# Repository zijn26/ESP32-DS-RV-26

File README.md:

Phần 1 . Hướng dẫn mở dự án kicad 

## 1️⃣ Giới thiệu

Project này được thiết kế bằng **KiCad** và bao gồm:

* **Schematic (sơ đồ nguyên lý)**
* **PCB Layout (mạch in nhiều lớp)**

Tài liệu này hướng dẫn cách mở và xem toàn bộ project bằng **KiCad** trên Windows, Linux hoặc macOS.

---

## 2️⃣ Phần mềm cần cài

Tải và cài đặt :

👉 **KiCad 7 hoặc KiCad 8 hoặc KiCad 9 **

Tải tại:
[https://www.kicad.org](https://www.kicad.org)

> ⚠ Khuyến nghị dùng Kicad 9, phiên bản mà project được tạo ra để tránh lỗi.

---

## 3️⃣ Cấu trúc thư mục project

Sau khi giải nén file ZIP, bạn sẽ thấy thư mục dạng:

```
MyProject/
├── esp32_module.kicad_pro
├── esp32_module.kicad_sch
├── esp32_module.kicad_pcb
├── MyFootprints.pretty
├── ul_myfootprinandsymbol
```

| File         | Chức năng           |
| ------------ | ------------------- |
| `.kicad_pro` | File project chính  |
| `.kicad_sch` | Schematic           |
| `.kicad_pcb` | PCB layout          |
| `.pretty`    | Footprint tùy chỉnh |
| `.kicad_sym` | Symbol tùy chỉnh    |
| `ul_xxxxxxx` | File chứa các footprint và symbol tùy chỉnh   |

---

## 4️⃣ Cách mở project trong KiCad

### Bước 1

Mở **KiCad**

---

### Bước 2

Nhấn **File → Open Project**

---

### Bước 3

Chọn file:

```
MyProject.kicad_pro
```

## 5️⃣ Mở Schematic (Sơ đồ nguyên lý)

Sau khi project mở:

Nhấn **Schematic Editor**

Sau đó sơ đồ nguyên lý sẽ xuất hiện.

---

## 6️⃣ Mở PCB Layout

Trong cửa sổ chính của KiCad:

Nhấn **PCB Editor**

PCB sẽ được mở ra với:

* Các lớp đồng (Top, Bottom, Inner layers)
* Via
* Plane
* Footprint

đang nằm **cùng thư mục với project**

Phần 2 : Thông tin về linh kiên sử dụng , giải thích về sơ đồ nguyên lý và mạch in

Thông tin về linh kiện sử dụng : 
Thầy hãy đọc file LINHKIENSUDUNG.md để biết thông tin chi tiết về linh kiện :
https://github.com/zijn26/ESP32-DS-RV-26/blob/main/LINHKIENSUDUNG.md
Thông tin về sơ đồ mạch và layout PCB , thày hãy đọc file GIAITHICH.md :
https://github.com/zijn26/ESP32-DS-RV-26/blob/main/GIAITHICH.md

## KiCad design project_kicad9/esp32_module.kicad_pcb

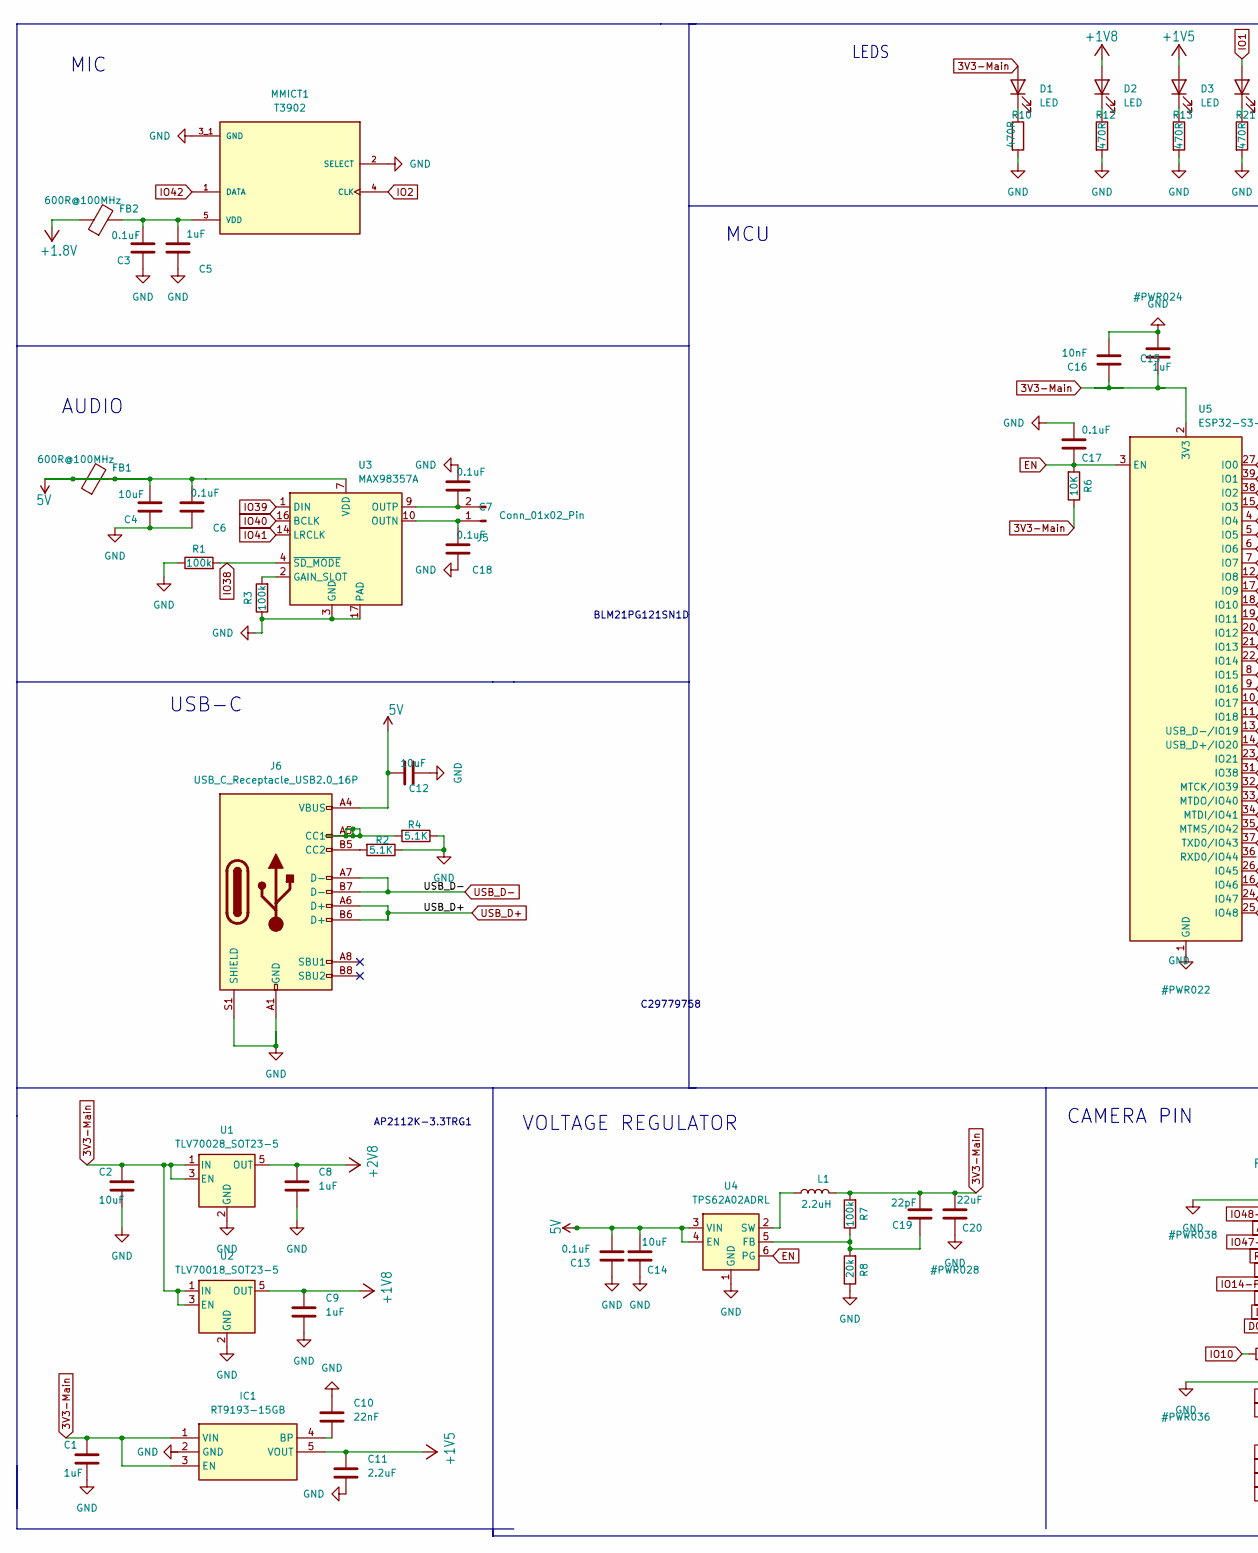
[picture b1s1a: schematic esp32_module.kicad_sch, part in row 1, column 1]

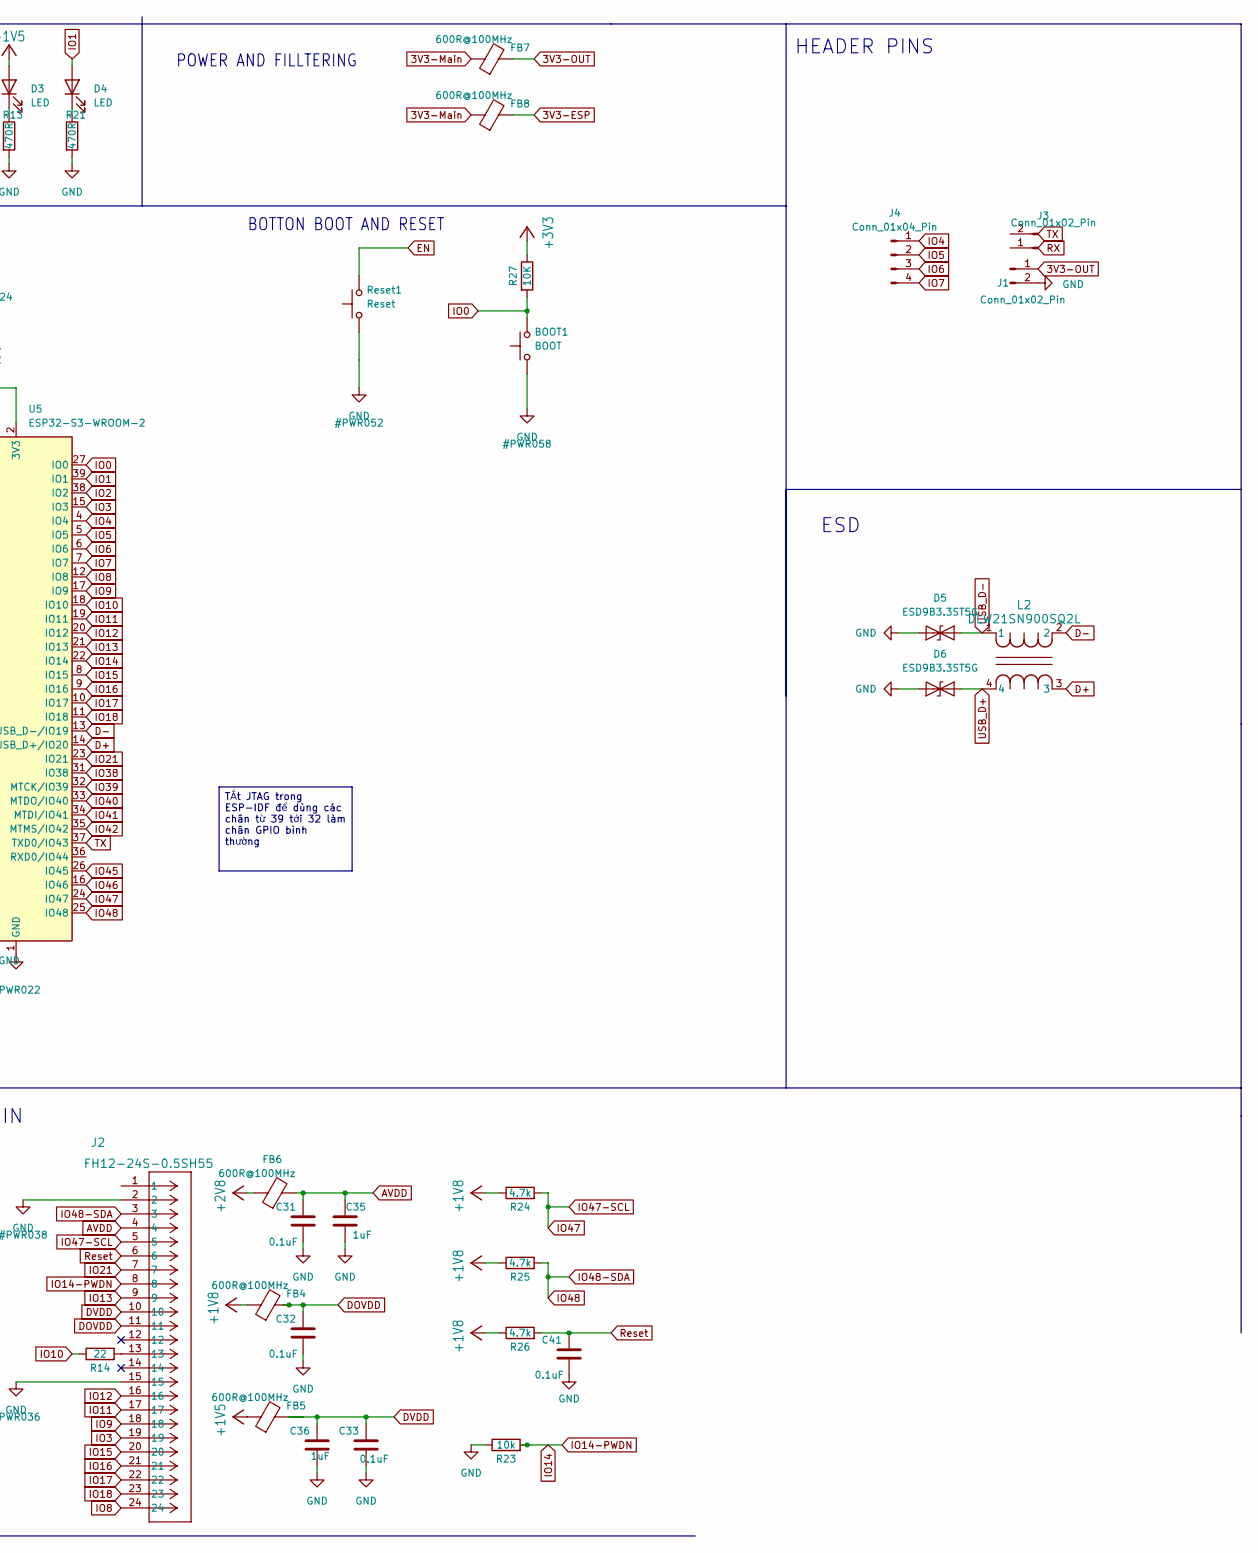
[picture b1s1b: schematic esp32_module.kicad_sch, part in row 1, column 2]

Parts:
BOOT1: BOOT; SW_Push_1P1T_XKB_TS-1187A; MNF PART NUMBER C318884; LCSC C318884
C1, C8, C9, C15, C35, C36: 1uF; C_0402_1005Metric; MNF PART NUMBER C52923; LCSC C52923
C2, C12, C14: 10uF; C_0402_1005Metric; MNF PART NUMBER C15525; LCSC C15525
C3, C13, C17, C31, C32, C33, C41: 0.1uF; C_0402_1005Metric; MNF PART NUMBER C1525; LCSC C1525
C4: 10uF; C_0402_1005Metric; MNF PART NUMBER C1525; LCSC C1525
C5: 1uF; C_0402_1005Metric; MNF PART NUMBER C15525; LCSC C15525
C6, C7, C18: 0.1uF; C_0402_1005Metric; MNF PART NUMBER C15525; LCSC C15525
C10: 22nF; C_0402_1005Metric; MNF PART NUMBER C15525; LCSC C15525
C11: 2.2uF; C_0402_1005Metric; MNF PART NUMBER C107369; LCSC C107369
C16: 10nF; C_0402_1005Metric; MNF PART NUMBER C15195; LCSC C15195
C19: 22pF; C_0402_1005Metric; MNF PART NUMBER C70464; LCSC C70464
C20: 22uF; C_0402_1005Metric; MNF PART NUMBER C105226; LCSC C105226
D1, D2, D3, D4: LED; LED_0603_1608Metric; MNF PART NUMBER C2286; LCSC C2286
D5, D6: ESD9B3.3ST5G; D_SOD-923
FB1, FB2, FB4, FB5, FB6, FB7, FB8: 600R@100MHz; BEADC1608X95N; MNF PART NUMBER C19330
IC1: RT9193-15GB; SOT94P280X100-5N; Manufacturer_Part_Number RT9193-15GB; Mouser Part Number 835-RT9193-15GB
J1, J3, J5: Conn_01x02_Pin; PinHeader_1x02_P2.54mm_Vertical
J2: FH12-24S-0.5SH55; CONN24X1_FH12-24S-0.5SH55_HIR; MNF PART NUMBER C202112
J4: Conn_01x04_Pin; PinHeader_1x04_P2.54mm_Vertical
J6: USB_C_Receptacle_USB2.0_16P; USB_C_Receptacle_HCTL_HC-TYPE-C-16P-01A
L1: 2.2uH; L_0402_1005Metric; MNF PART NUMBER C13595; LCSC C13595
L2: DLW21SN900SQ2L; IND_DLW21S_0805_MUR-M
MMICT1: T3902; MIC_T3902; PARTREV 1.0
R1, R3: 100k; R_0402_1005Metric; MNF PART NUMBER C17168; LCSC C17168
R2, R4: 5.1K; R_0402_1005Metric; MNF PART NUMBER C25905; LCSC C25905
R6, R27: 10K; R_0402_1005Metric; MNF PART NUMBER C25744; LCSC C25744
R7: 100k; R_0402_1005Metric; MNF PART NUMBER C25744; LCSC C25744
R8: 20k; R_0402_1005Metric; MNF PART NUMBER C25744; LCSC C25744
R10, R12, R13, R21: 470R; R_0402_1005Metric; MNF PART NUMBER C25117; LCSC C25117
R14: 22; R_0402_1005Metric; MNF PART NUMBER C25092; LCSC C25744
R23: 10k; R_0402_1005Metric; MNF PART NUMBER C25744; LCSC C25744
R24, R25, R26: 4.7k; R_0402_1005Metric; MNF PART NUMBER C25900; LCSC C25900
Reset1: Reset; SW_Push_1P1T_XKB_TS-1187A; MNF PART NUMBER C318884; LCSC C318884
U1: TLV70028_SOT23-5; SOT-23-5; MNF PART NUMBER C507266
U2: TLV70018_SOT23-5; SOT-23-5; MNF PART NUMBER C79924
U3: MAX98357A; Max98753-ETE
U4: TPS62A02ADRL; SOT-563; MNF PART NUMBER C5820994
U5: ESP32-S3-WROOM-2

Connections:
3V3-Main: C1.1, C2.1, C15.1, C16.1, C19.2, C20.2, D1.2 (A), FB7.1, FB8.1, IC1.1 (VIN), IC1.3 (EN), L1.2, R6.1, R7.2, U1.1 (IN), U1.3 (EN), U2.1 (IN), U2.3 (EN), U5.2 (3V3)
3V3-OUT: FB7.2, J1.1
5V: C4.2, C6.2, C12.1, C13.2, C14.2, FB1.1, FB1.2, J6.A4 (VBUS), J6.A9 (VBUS), J6.B4 (VBUS), J6.B9 (VBUS), U3.7 (VDD), U3.8 (VDD), U4.3 (VIN), U4.4 (EN)
+1.8V: FB2.1
+1V5: C11.2, D3.2 (A), FB5.1, IC1.5 (VOUT)
+1V8: C9.2, D2.2 (A), FB4.1, R24.1, R25.1, R26.1, U2.5 (OUT)
+2V8: C8.1, FB6.1, U1.5 (OUT)
+3V3: R27.1
AVDD: C31.1, C35.1, FB6.2, J2.4
D+: L2.3, U5.14 (USB_D+/IO20)
D-: L2.2, U5.13 (USB_D-/IO19)
DOVDD: C32.1, FB4.2, J2.11
DVDD: C33.1, C36.1, FB5.2, J2.10
EN: C17.1, R6.2, Reset1.2, U4.6 (PG), U5.3 (EN)
GND: BOOT1.1, C1.2, C2.2, C3.1, C4.1, C5.1, C6.1, C7.2, C8.2, C9.1, C10.2, C11.1, C12.2, C13.1, C14.1, C15.2, C16.2, C17.2, C18.1, C20.1, C31.2, C32.2, C33.2, C35.2, C36.2, C41.2, D5.1 (A1), D6.1 (A1), J1.2, J2.2, J2.15, J6.A1 (GND), J6.A12 (GND), J6.B1 (GND), J6.B12 (GND), J6.S1 (SHIELD), MMICT1.2 (SELECT), MMICT1.3_1 (GND), MMICT1.3_2 (GND), R1.1, R2.1, R3.1, R4.1, R8.1, R10.2, R12.2, R13.2, R21.2, R23.1, Reset1.1, U1.2 (GND), U2.2 (GND), U3.3 (GND), U3.11 (GND), U3.15 (GND), U3.17 (PAD), U4.1 (GND), U5.1 (GND), U5.40 (GND), U5.41 (GND)
IO0: BOOT1.2, R27.2, U5.27 (IO0)
IO1: D4.2 (A), U5.39 (IO1)
IO2: MMICT1.4 (CLK), U5.38 (IO2)
IO3: J2.19, U5.15 (IO3)
IO4: J4.1, U5.4 (IO4)
IO5: J4.2, U5.5 (IO5)
IO6: J4.3, U5.6 (IO6)
IO7: J4.4, U5.7 (IO7)
IO8: J2.24, U5.12 (IO8)
IO9: J2.18, U5.17 (IO9)
IO10: R14.1, U5.18 (IO10)
IO11: J2.17, U5.19 (IO11)
IO12: J2.16, U5.20 (IO12)
IO13: J2.9, U5.21 (IO13)
IO14: J2.8, R23.2, U5.22 (IO14)
IO15: J2.20, U5.8 (IO15)
IO16: J2.21, U5.9 (IO16)
IO17: J2.22, U5.10 (IO17)
IO18: J2.23, U5.11 (IO18)
IO21: J2.7, U5.23 (IO21)
IO38: R1.2, U3.4 (~SD_MODE), U5.31 (IO38)
IO39: U3.1 (DIN), U5.32 (MTCK/IO39)
IO40: U3.16 (BCLK), U5.33 (MTDO/IO40)
IO41: U3.14 (LRCLK), U5.34 (MTDI/IO41)
IO42: MMICT1.1 (DATA), U5.35 (MTMS/IO42)
IO45: U5.26 (IO45)
IO46: U5.16 (IO46)
IO47: J2.5, R24.2, U5.24 (IO47)
IO48: J2.3, R25.2, U5.25 (IO48)
unnamed: D1.1 (K), R10.1
unnamed: D2.1 (K), R12.1
unnamed: D3.1 (K), R13.1
unnamed: D4.1 (K), R21.1
unnamed: C10.1, IC1.4 (BP)
unnamed: J2.13, R14.2
unnamed: C18.2, J5.1, U3.10 (OUTN)
unnamed: C7.1, J5.2, U3.9 (OUTP)
unnamed: J6.A5 (CC1), R4.2
unnamed: J6.B5 (CC2), R2.2
unnamed: C3.2, C5.2, FB2.2, MMICT1.5 (VDD)
unnamed: R3.2, U3.2 (GAIN_SLOT)
unnamed: C19.1, R7.1, R8.2, U4.5 (FB)
unnamed: L1.1, U4.2 (SW)
Reset: C41.1, J2.6, R26.2
TX: U5.37 (TXD0/IO43)
USB_D+: D6.2 (A2), J6.A6 (D+), J6.B6 (D+), L2.4
USB_D-: D5.2 (A2), J6.A7 (D-), J6.B7 (D-), L2.1

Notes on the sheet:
VOLTAGE REGULATOR
AP2112K-3.3TRG1
C29779758
LEDS
MCU
HEADER PINS
ESD
POWER AND FILLTERING
AUDIO
BOTTON BOOT AND RESET
MIC
CAMERA PIN
USB-C
BLM21PG121SN1D
TẮt JTAG trong ESP-IDF để dùng các chân từ 39 tới 32 làm chân GPIO bình thường

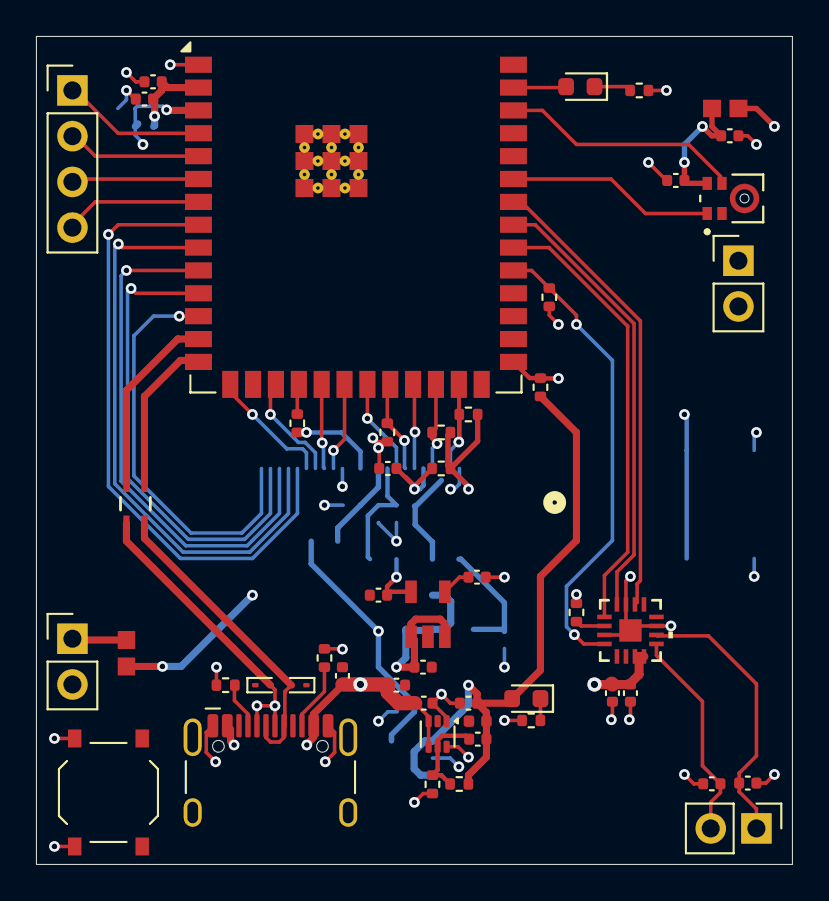
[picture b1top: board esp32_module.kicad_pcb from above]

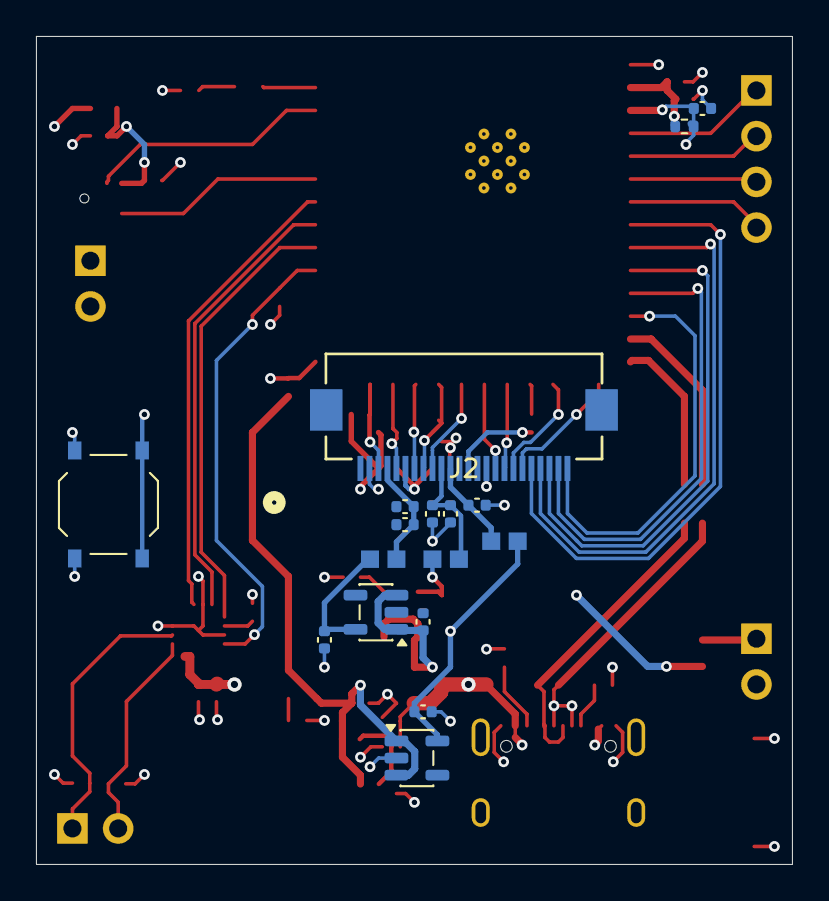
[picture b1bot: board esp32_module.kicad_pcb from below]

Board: 4 copper layers, 42.0 x 46.0 mm, 67 parts (17 on the bottom side), 55 nets.

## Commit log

2026-01-12 TEST
2026-01-12 ADD readme
2026-01-12 add Image for readme
2026-01-12 add linh kien su dung readme
2026-01-12 add readme giai thich
2026-01-12 sua readme
2026-01-12 add project kicad 9
